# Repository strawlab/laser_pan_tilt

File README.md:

laser-pan-tilt
==============

laser-pan-tilt

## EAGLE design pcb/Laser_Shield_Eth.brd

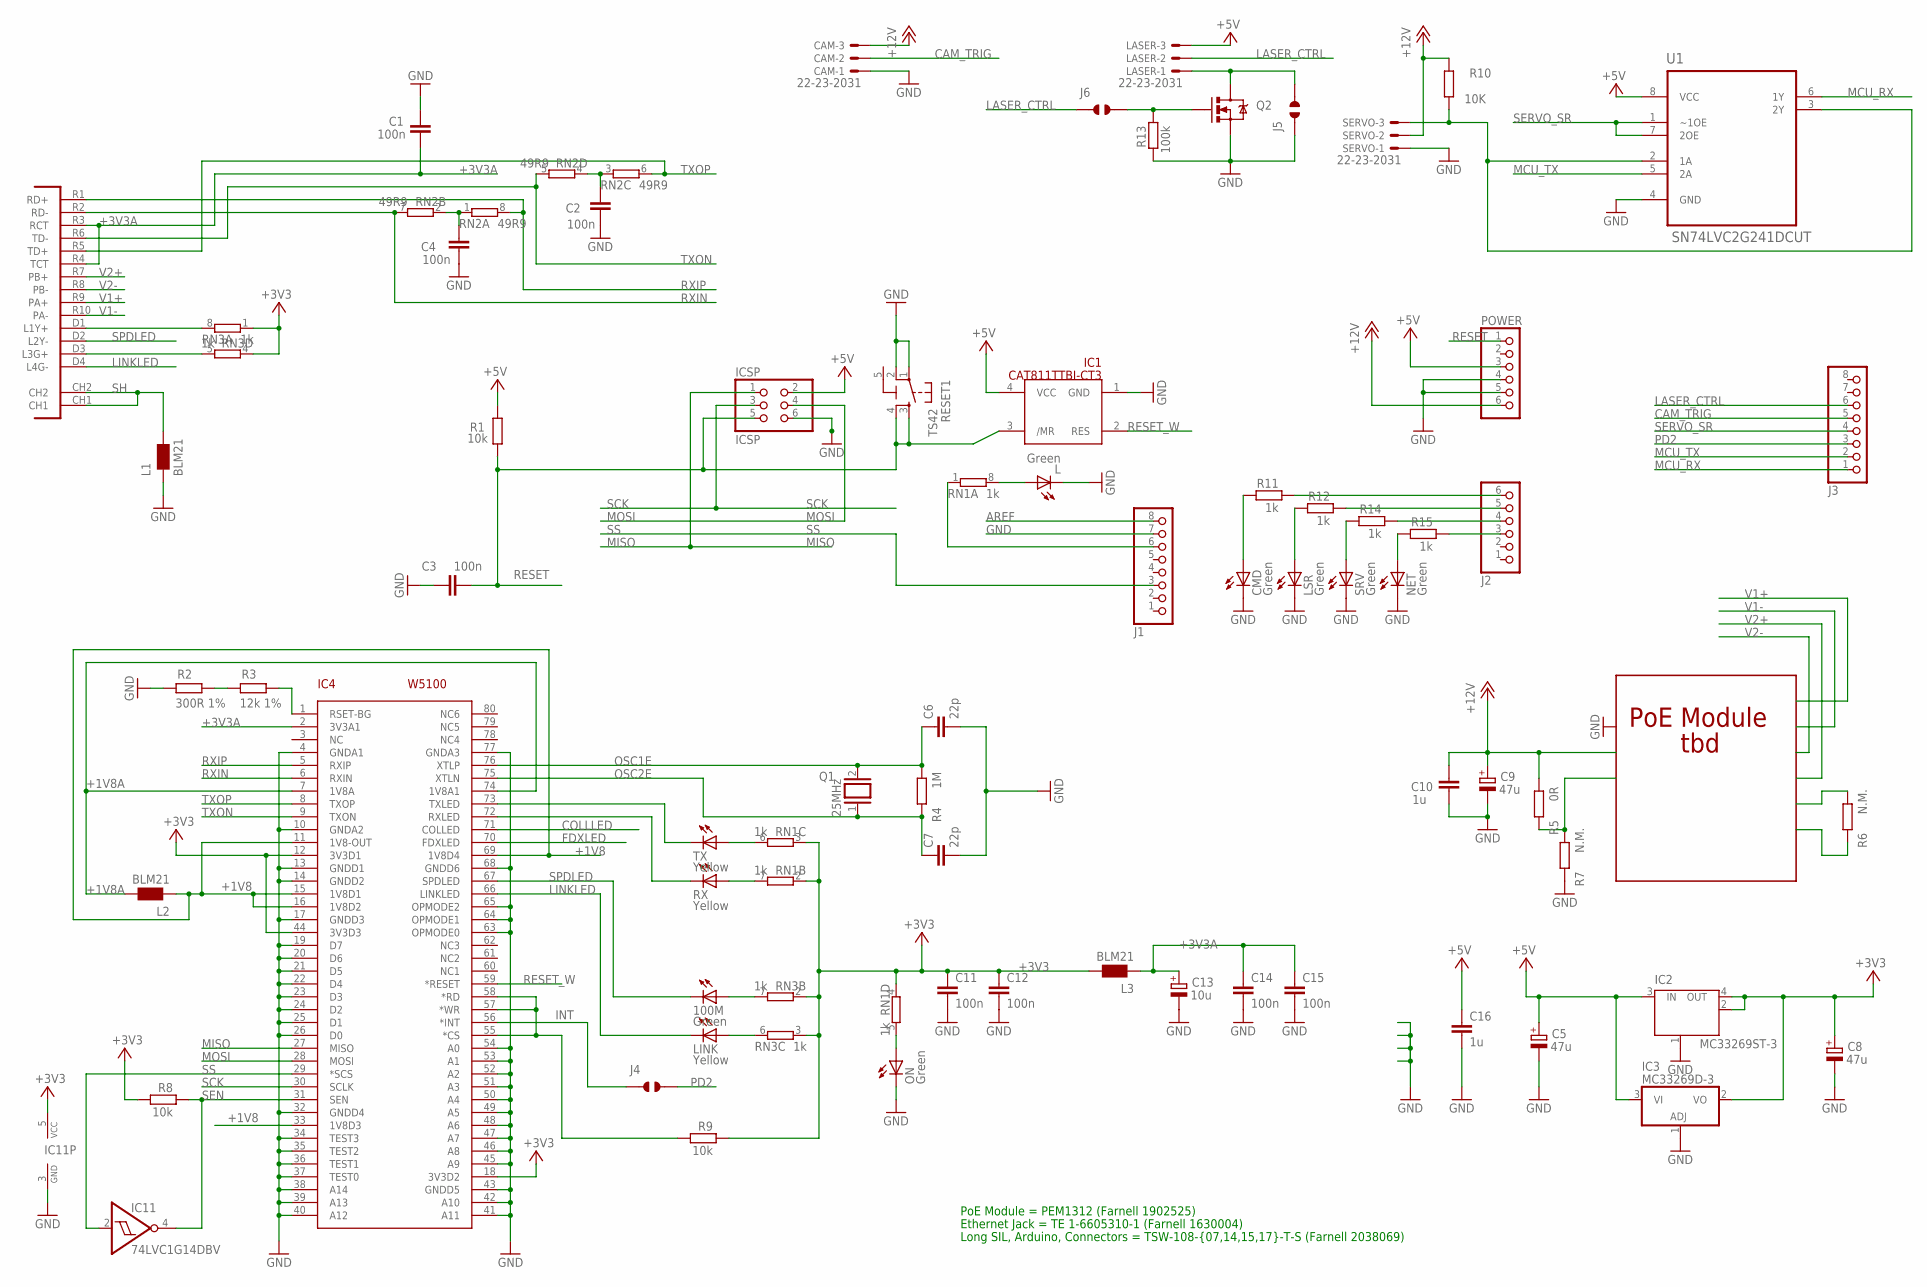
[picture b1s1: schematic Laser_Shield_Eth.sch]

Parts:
100M: Green; CHIPLED_0805
C1, C2, C3, C4, C11, C12, C14, C15: 100n; C0603-ROUND
C5, C8, C9: 47u; PANASONIC_D
C6, C7: 22p; C0603-ROUND
C10, C16: 1u; C0603-ROUND
C13: 10u; SMC_B
CAM: 22-23-2031
CMD: Green; CHIPLED_0805
IC1: CAT811TTBI-CT3; SOT143; MPN STM812LW16F
IC2: MC33269ST-3; SOT223
IC3: MC33269D-3; DPACK
IC4: W5100; SQFP-S-10X10-80
IC11: 74LVC1G14DBV; SOT23-5; MPN SN74LVC1G14DBVT
ICSP: ICSP; 2X03
J1, J3: PINHD-1X8; 1X08
J2: PINHD-1X6; 1X06
J4, J5, J6: JUMPER_SOLDER_1X2
L: Green; CHIPLED_0805
L1, L2, L3: BLM21; 0805
LASER: 22-23-2031
LINK: Yellow; CHIPLED_0805
LSR: Green; CHIPLED_0805
NET: Green; CHIPLED_0805
ON: Green; CHIPLED_0805
POWER: PINHD-1X6; 1X06
Q1: 25MHz; QS
Q2: MOSFET-NCHANNELSMD; SOT23-3
R1, R8, R9: 10k; R0603-ROUND
R2: 300R 1%; R0603-ROUND
R3: 12k 1%; R0603-ROUND
R4: 1M; R0603-ROUND
R5: 0R; R0603-ROUND
R6, R7: N.M.; R0603-ROUND
R10: 10K; R0603-ROUND
R11, R12, R14, R15: 1k; R0603-ROUND
R13: 100k; R0603-ROUND
RESET1: TS42
RN1, RN3: 1k; CAY16; MPN CAY16-102J4LF
RN2: 49R9; CAY16; MPN CAY16-49R9F4LF
RX: Yellow; CHIPLED_0805
SERVO: 22-23-2031; MPN 22-03-5035
SRV: Green; CHIPLED_0805
TX: Yellow; CHIPLED_0805
U1: SN74LVC2G241DCUT; SOP50P310X90-8N
U$1: POE-RJ45

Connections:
5-GND: RESET1.5 (5-GND)
+1V8: IC4.11 (1V8-OUT), IC4.15 (1V8D1), IC4.16 (1V8D2), IC4.33 (1V8D3), IC4.69 (1V8D4), L2.1
+1V8A: IC4.7 (1V8A), IC4.74 (1V8A1), L2.2
+3V3: C8.+, C11.1, C12.1, IC2.2 (OUT), IC2.4 (OUT), IC3.2 (VO), IC4.12 (3V3D1), IC4.18 (3V3D2), IC4.44 (3V3D3), IC11.5 (VCC), L3.2, R8.1, R9.2, RN1.2 (1), RN1.3 (1), RN1.4 (1), RN3.1, RN3.2 (1), RN3.3 (1), RN3.4 (1)
+3V3A: C1.1, C13.+, C14.1, C15.1, IC4.2 (3V3A1), L3.1, U$1.R3 (RCT), U$1.R4 (TCT)
+5V: C5.+, C16.1, IC1.4 (VCC), IC2.3 (IN), IC3.3 (VI), ICSP.2, LASER.3, POWER.3, R1.2, U1.8 (VCC)
+12V: C9.+, C10.2, CAM.3, POWER.6, R5.1, R10.1, SERVO.2
AREF: J1.8
CAM_TRIG: CAM.2, J3.5
COLLLED: IC4.71 (COLLED)
FDXLED: IC4.70 (FDXLED)
GND: C1.2, C2.1, C3.2, C4.1, C5.-, C6.2, C7.2, C8.-, C9.-, C10.1, C11.2, C12.2, C13.-, C14.2, C15.2, C16.2, CAM.1, CMD.C, IC1.1 (GND), IC2.1 (GND/ADJ), IC3.1 (ADJ), IC4.4 (GNDA1), IC4.10 (GNDA2), IC4.13 (GNDD1), IC4.14 (GNDD2), IC4.17 (GNDD3), IC4.19 (D7), IC4.20 (D6), IC4.21 (D5), IC4.22 (D4), IC4.23 (D3), IC4.24 (D2), IC4.25 (D1), IC4.26 (D0), IC4.32 (GNDD4), IC4.34 (TEST3), IC4.35 (TEST2), IC4.36 (TEST1), IC4.37 (TEST0), IC4.38 (A14), IC4.39 (A13), IC4.40 (A12), IC4.41 (A11), IC4.42 (A10), IC4.43 (GNDD5), IC4.45 (A9), IC4.46 (A8), IC4.47 (A7), IC4.48 (A6), IC4.49 (A5), IC4.50 (A4), IC4.51 (A3), IC4.52 (A2), IC4.53 (A1), IC4.54 (A0), IC4.63 (OPMODE0), IC4.64 (OPMODE1), IC4.65 (OPMODE2), IC4.68 (GNDD6), IC4.77 (GNDA3), IC11.3 (GND), ICSP.6, J1.7, J5.1, L.C, L1.1, LSR.C, NET.C, ON.C, POWER.4, POWER.5, Q2.2 (S), R2.2, R7.2, R13.1, RESET1.1, RESET1.2, SERVO.1, SRV.C, U1.4 (GND)
INT: IC4.56 (*INT), J4.1
LASER_CTRL: J3.6, J6.1, LASER.2
LINKLED: IC4.66 (LINKLED), LINK.C, U$1.D4 (L4G-)
MCU_RX: J3.1, U1.6 (1Y)
MCU_TX: J3.2, U1.5 (2A)
MISO: IC4.27 (MISO), ICSP.1
MOSI: IC4.28 (MOSI), ICSP.4
unnamed: L.A, RN1.8 (2)
unnamed: RN3.5 (2), U$1.D3 (L3G+)
unnamed: RN3.8 (2), U$1.D1 (L1Y+)
unnamed: CMD.A, R11.1
unnamed: LSR.A, R12.1
unnamed: IC4.73 (TXLED), TX.C
unnamed: IC4.72 (RXLED), RX.C
unnamed: ON.A, RN1.5 (2)
unnamed: RN1.6 (2), TX.A
unnamed: C2.2, RN2.3 (1), RN2.4 (1)
unnamed: R14.1, SRV.A
unnamed: NET.A, R15.1
unnamed: J6.2, Q2.1 (G), R13.2
unnamed: J5.2, LASER.1, Q2.3 (D)
unnamed: J1.6, RN1.1
unnamed: J2.6, R11.2
unnamed: J2.5, R12.2
unnamed: J2.4, R14.2
unnamed: J2.3, R15.2
unnamed: RN1.7 (2), RX.A
unnamed: 100M.A, RN3.7 (2)
unnamed: LINK.A, RN3.6 (2)
unnamed: C4.2, RN2.1, RN2.2 (1)
unnamed: R2.1, R3.2
unnamed: IC4.1 (RSET-BG), R3.1
unnamed: R5.2, R7.1
unnamed: IC4.55 (*CS), IC4.57 (*WR), IC4.58 (*RD), R9.1
OSC1E: C6.1, IC4.76 (XTLP), Q1.2, R4.1
OSC2E: C7.1, IC4.75 (XTLN), Q1.1, R4.2
PD2: J3.3, J4.2
RESET: C3.1, IC1.3 (/MR), ICSP.5, POWER.1, R1.1, RESET1.3, RESET1.4
RESET_W: IC1.2 (RES), IC4.59 (*RESET)
RXIN: IC4.6 (RXIN), RN2.7 (2), U$1.R2 (RD-)
RXIP: IC4.5 (RXIP), RN2.8 (2), U$1.R1 (RD+)
SCK: IC4.30 (SCLK), ICSP.3
SEN: IC4.31 (SEN), IC11.4 (O), R8.2
SERVO_DATA: R10.2, SERVO.3, U1.2 (1A), U1.3 (2Y)
SERVO_SR: J3.4, U1.1 (~1OE), U1.7 (2OE)
SH: L1.2, U$1.CH1, U$1.CH2
SPDLED: 100M.C, IC4.67 (SPDLED), U$1.D2 (L2Y-)
SS: IC4.29 (*SCS), IC11.2 (I), J1.3
TXON: IC4.9 (TXON), RN2.5 (2), U$1.R6 (TD-)
TXOP: IC4.8 (TXOP), RN2.6 (2), U$1.R5 (TD+)
V1+: U$1.R9 (PA+)
V1-: U$1.R10 (PA-)
V2+: U$1.R7 (PB+)
V2-: U$1.R8 (PB-)

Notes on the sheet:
PoE Module
tbd
PoE Module = PEM1312 (Farnell 1902525)
Ethernet Jack = TE 1-6605310-1 (Farnell 1630004)
Long SIL, Arduino, Connectors = TSW-108-{07,14,15,17}-T-S (Farnell 2038069)

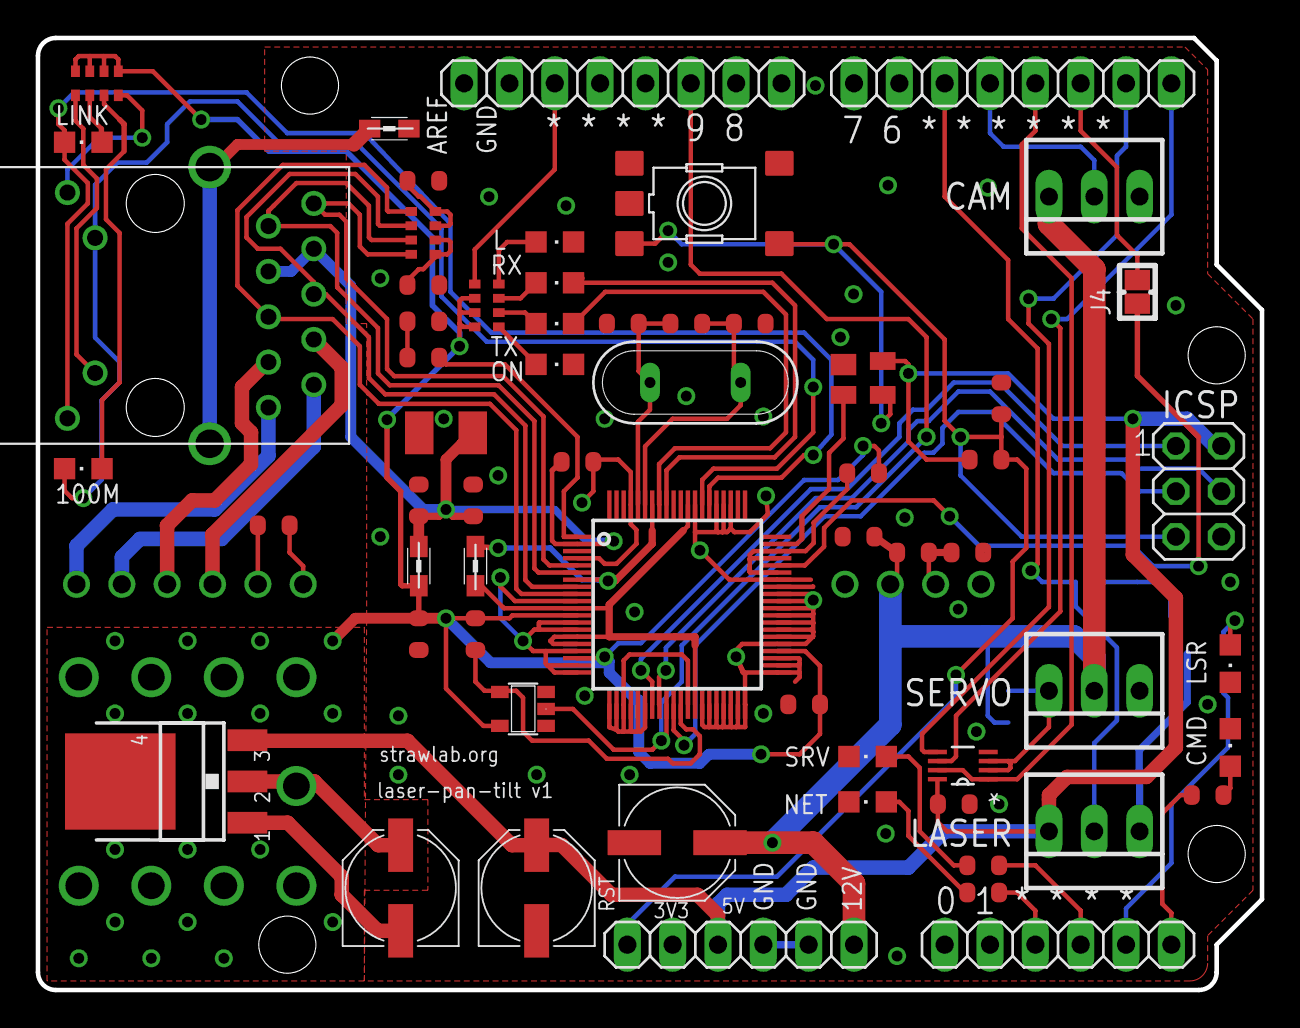
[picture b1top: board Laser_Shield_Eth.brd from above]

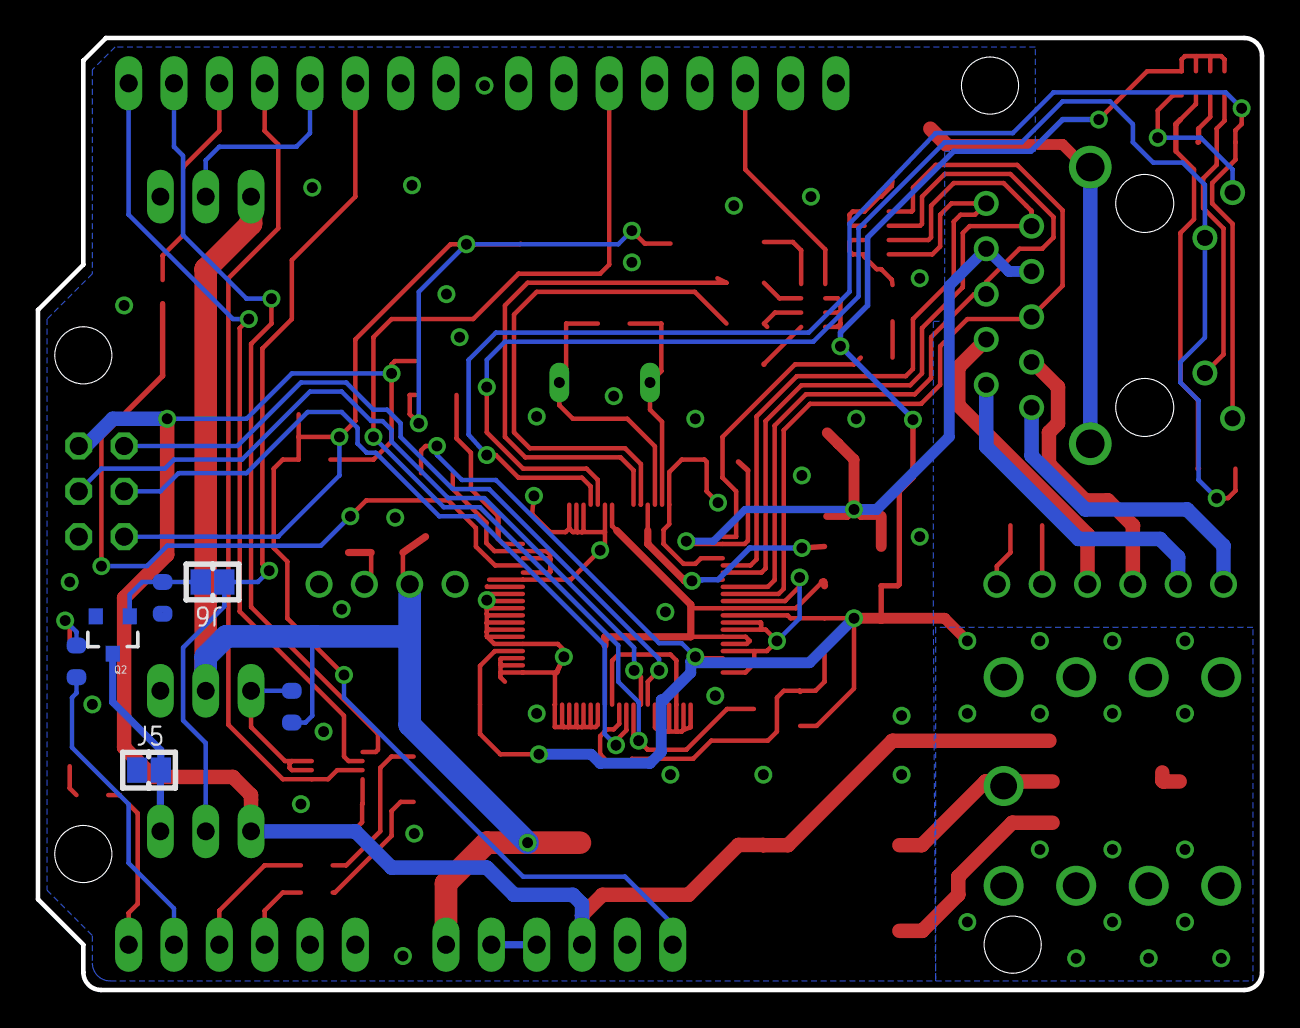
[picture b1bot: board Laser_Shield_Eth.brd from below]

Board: 2 copper layers, 68.6 x 53.3 mm, 68 parts (6 on the bottom side), 58 nets.

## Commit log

2012-08-08 Import lightly modified poor quality Dynamixel library
2012-08-08 Skeleton ethernet PTC
2012-08-16 does something
2012-08-30 PTC: use arduino-mk, separate config
2012-08-30 gitignores
2012-08-30 some python wrappers
2012-08-30 examples
2012-10-23 parts
2012-10-23 add pcb
2012-10-24 pcb done?
2012-10-24 silver circuits DRC
2012-10-29 rewrite most of the terrible old arduino Dynamixel library
2012-10-29 more stability improvements
2012-10-29 great stability improvements
2012-10-30 small stability improvements
2012-10-30 update python API
2012-10-31 pcb: more LEDS
2012-11-02 pcb: project
2012-11-02 libs
2012-11-05 final pcb eth socket fixes
2012-11-05 final pcb airwires tidy
2012-12-13 pcb: more part numbers
2013-01-16 note some resistor values and add TODO
2013-01-17 port lib_robotis.py to argparse, make series explicit
2013-01-17 implement delay when reading registers
2013-01-18 test greater range
2013-01-18 swap IDs of servos to minimise programming
2013-01-18 much simplification of the original bad c++ Dynamixel API
2013-01-21 be more useful inside ipython
2013-01-22 seems to work
2013-01-22 ptc.py: better comms checking
2013-01-22 use the net led to indication connection
2013-01-22 undefined constants will provide HW safety
2013-01-22 make unary stack
2013-01-22 gitignore
2013-02-22 import related nodes from flycave

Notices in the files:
parts and their libraries:
SparkFun-DiscreteSemi: Licensing: CC v3.0 Share-Alike You are welcome to use this library for commercial purposes.
